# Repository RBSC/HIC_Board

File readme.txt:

--------------------------------------------------------------------------------
HIC Board version 1.2
Copyright (c) 2021-2023 RBSC
Last updated: 21.09.2023
--------------------------------------------------------------------------------

About
-----

It's a well-known fact that certain MSX2/2+ computers have a so-called "HIC Board" - the special "Hybrid IC" daughterboard that is
mounted onto the MSX computer's motherboard and provides certain functionality. This functionality is as follows:

 - converts RGBS signals to composite video
 - pre-amplifies and buffers audio
 - mutes audio at startup and on pause to prevent clicks
 - mixes all audio inputs
 - amplifies and buffers the cassette interface signals
 - buffers cassette interface's relay operations

This board is known to be installed in the following MSX computers:

 - Sony HB-F1II
 - Sony HB-F1XD
 - Sony HB-F1XV
 - Sony HB-F1XDJ
 - Sony HB-F1XDmkII
 - Panasonic FS-A1mkII
 - Panasonic FS-A1F
 - Kawai KMC-5000 (Panasonic FS-A1F OEM)

Normally, the board works just fine, but there's a problem with 3 electrolytic capacitors - they leak and damage the board,
sometimes beyond repair. Fixing the leaked boards is difficult as some components can separate from the corroded solder pads,
some tracks can be corroded under the CXA chip resulting in the board's malfunction.

The original HIC board's schematics and layout can be found here:
http://elec-junker-p2.blog.jp/MITSUMI%20EMC-NX0039_REV02_PU.pdf

HIC Board's Redesign
--------------------

Taking into account all the above listed problems, it was decided to clone the HIC board and at the same time add the following
improvements:

 - use a better and commonly available encoder chip CXA2075
 - add s-video output capability
 - try to get rid of the original 4069UBF chip's dependency
 - make the HIC board detachable

It was also desired to get rid of the 2 special components: IMN10 and FMW1, but they appeared to be still available for purchasing,
so they remained on the redesigned board.

During the redesign there appeared a few problems. The 4069UBF chip from Toshiba was used by the original engineers as an amplifier,
so the board's audio and cassette interface operations were dependent on certain features of that chip. When trying to replace this
chip with similar ones, for example 74LS04 or 74HCT04, the audio functionality was crippled. The only possible replacement appears
to be 74HC04 with 68pF capacitor added between pins 3 and 7 (GND). See the "74hc04_fix.jpg" image in the Pics folder.

The optional resistor R35 should not be installed unless the cassette input circuit doesn't work as desired.

Please note that R39 should be 0 Ohm resistor for all computers except for HB-F1XDJ. On that particular computer R39 should
be 220k.

Where to buy parts
------------------

At the time of this readme's creation the parts are available from the following sellers:

 - pin headers (male and female): https://www.aliexpress.com/item/4001122376295.html
 - CXA2075 encoder: https://www.aliexpress.com/item/33020885081.html
 - 4069UBF: https://www.aliexpress.com/item/1005002494421415.html
 - 68uH inductor: https://www.aliexpress.com/item/1005002963165525.html
 - LMV358M amplifier: https://www.aliexpress.com/item/4001116443945.html
 - 68pF trim capacitor: https://www.aliexpress.com/item/4000222152928.html
 - 2SA1037 transistor: https://www.aliexpress.com/item/1005002503421569.html
 - 2SC2411 transistor: https://www.aliexpress.com/item/1005004568437670.html
 - IMN10: https://www.aliexpress.com/item/1005004322498640.html
 - FMW1: https://www.ebay.com/itm/325038640119 or from Wierzbowsky (RBSC)

The resistors and capacitors 0805 and 1210 form factor can be ordered from any reasonable seller. The boards can be ordered from the
JLCPCB.COM factory.

IMPORTANT!
----------

The board hasn't been tested on all available MSX2/MSX2+ computers that are listed above. So far, the board was proved to be working
well on Panasonic A1 series computers, as well as on Sony F1-XV. There's still no feedback from some people who bought the HIC board
kits for other computers. As a result, the project's status is still WIP (work in progress).

The boards version 1.0 and 1.1 have an error that results in problems with PSG and FM sound on Sony HB-F1XDJ. The information on how
to fix the problem with those boards can be found in the "v1_board_fix.jpg" image file. One trace needs to be cut, 2 pads need to be
connected and C20 needs to be replaced with 39pF capacitor.

The RBSC provides all the files and information for free, without any liability (see the disclaimer.txt file). The provided information,
software or hardware must not be used for commercial purposes unless permitted by the RBSC. Producing a small amount of bare boards for
personal projects and selling the rest of the batch is allowed without the permission of RBSC.

When the sources of the tools are used to create alternative projects, please always mention the original source and the copyright!

Contact information
-------------------

The members of RBSC group Tnt23, Wierzbowsky, Pyhesty, Ptero, GreyWolf, SuperMax, VWarlock and DJS3000 can be contacted via the group's
e-mail address:

info@rbsc.su

The group's coordinator could be reached via this e-mail address:

admin@rbsc.su

The group's website can be found here:

https://rbsc.su/
https://rbsc.su/ru

The RBSC's hardware repository can be found here:

https://github.com/rbsc

The RBSC's 3D model repository can be found here:

https://www.thingiverse.com/groups/rbsc/things

-= ! MSX FOREVER ! =-

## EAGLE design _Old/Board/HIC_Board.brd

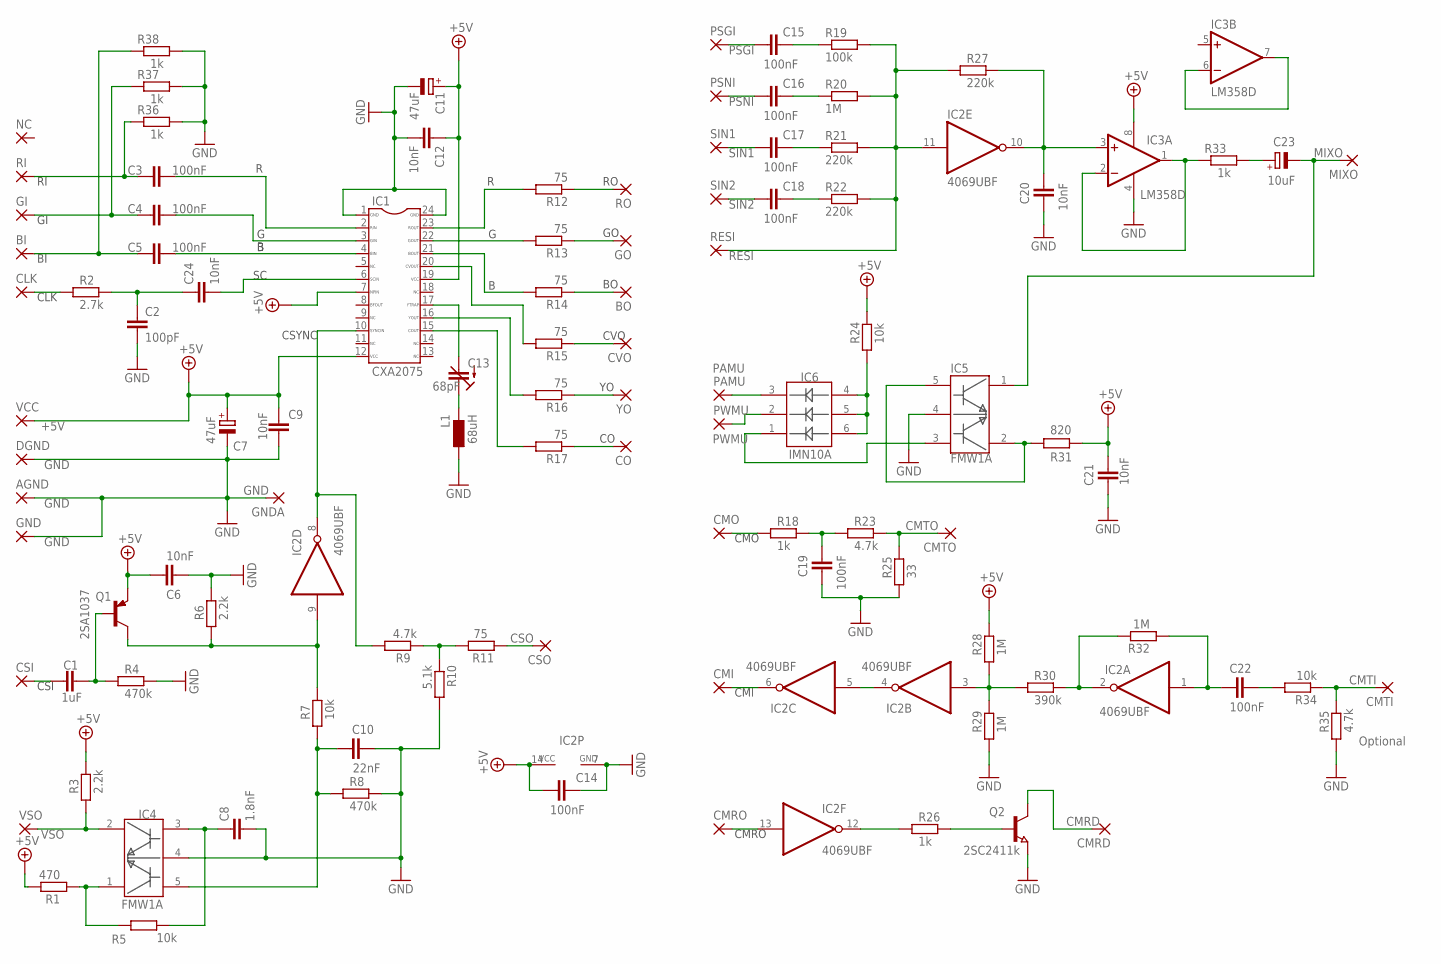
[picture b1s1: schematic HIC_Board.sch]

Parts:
AGND: HICPADSMD; SMD1,27-2,54
BI: HICPADSMD; SMD1,27-2,54
BO: HICPADSMD; SMD1,27-2,54
C1: 1uF; C1210
C2: 100pF; C0805
C3, C4, C5, C14, C15, C16, C17, C18, C19, C22: 100nF; C0805
C6, C9, C12, C20, C21, C24: 10nF; C0805
C7, C11: 47uF; SMC_B
C8: 1.8nF; C0805
C10: 22nF; C0805
C13: 68pF; CTRIMTZ03
C23: 10uF; SMC_B
CLK: HICPADSMD; SMD1,27-2,54
CMI: HICPADSMD; SMD1,27-2,54
CMO: HICPADSMD; SMD1,27-2,54
CMRD: HICPADSMD; SMD1,27-2,54
CMRO: HICPADSMD; SMD1,27-2,54
CMTI: HICPADSMD; SMD1,27-2,54
CMTO: HICPADSMD; SMD1,27-2,54
CO: HICPADSMD; SMD1,27-2,54
CSI: HICPADSMD; SMD1,27-2,54
CSO: HICPADSMD; SMD1,27-2,54
CVO: HICPADSMD; SMD1,27-2,54
DGND: HICPADSMD; SMD1,27-2,54
GI: HICPADSMD; SMD1,27-2,54
GND: HICPADSMD; SMD1,27-2,54
GNDA: HICPADSMD; SMD1,27-2,54
GO: HICPADSMD; SMD1,27-2,54
IC1: CXA2075; SOP24
IC2: 4069UBF; SO14
IC3: LM358D; SO08
IC4, IC5: FMW1A; SMT5
IC6: IMN10A; SMT6
L1: 68uH; L3225M
MIXO: HICPADSMD; SMD1,27-2,54
NC: HICPADSMD; SMD1,27-2,54
PAMU: HICPADSMD; SMD1,27-2,54
PSGI: HICPADSMD; SMD1,27-2,54
PSNI: HICPADSMD; SMD1,27-2,54
PWMU: HICPADSMD; SMD1,27-2,54
Q1: 2SA1037; SOT23
Q2: 2SC2411k; SOT23
R1: 470; R0805
R2: 2.7k; R0805
R3, R6: 2.2k; R0805
R4, R8: 470k; R0805
R5, R7, R24, R34: 10k; R0805
R9, R23, R35: 4.7k; R0805
R10: 5.1k; R0805
R11, R12, R13, R14, R15, R16, R17: 75; R0805
R18, R26, R33, R36, R37, R38: 1k; R0805
R19: 100k; R0805
R20, R28, R29, R32: 1M; R0805
R21, R22, R27: 220k; R0805
R25: 33; R0805
R30: 390k; R0805
R31: 820; R0805
RESI: HICPADSMD; SMD1,27-2,54
RI: HICPADSMD; SMD1,27-2,54
RO: HICPADSMD; SMD1,27-2,54
SIN1, SIN2: HICPADSMD; SMD1,27-2,54
VCC: HICPADSMD; SMD1,27-2,54
VSO: HICPADSMD; SMD1,27-2,54
YO: HICPADSMD; SMD1,27-2,54

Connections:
+5V: C6.1, C7.+, C9.2, C11.+, C12.1, C14.2, C21.2, IC1.7, IC1.12, IC1.19, IC2.14 (VCC), IC3.8 (V+), Q1.2 (E), R1.2, R3.2, R24.2, R28.2, R31.2, VCC.1
CMRD: CMRD.1, Q2.3 (C)
CMTI: CMTI.1, R34.1, R35.2
CMTO: CMTO.1, R23.2, R25.2
CSO: CSO.1, R11.1
GND: AGND.1, C2.1, C6.2, C7.-, C8.1, C9.1, C10.2, C11.-, C12.2, C14.1, C19.2, C20.2, C21.1, DGND.1, GND.1, GNDA.1, IC1.1, IC1.24, IC2.7 (GND), IC3.4 (V-), IC4.4, IC5.4, L1.1, Q2.2 (E), R4.2, R6.2, R8.2, R10.2, R25.1, R29.1, R35.1, R36.2, R37.2, R38.2
MIXO: C23.-, IC5.1, MIXO.1
unnamed: IC1.23, R12.2
unnamed: IC1.22, R13.2
unnamed: IC1.21, R14.2
unnamed: R12.1, RO.1
unnamed: GO.1, R13.1
unnamed: C3.1, R36.1, RI.1
unnamed: C4.1, GI.1, R37.1
unnamed: BO.1, R14.1
unnamed: R16.1, YO.1
unnamed: CVO.1, R15.1
unnamed: C2.2, C24.2, R2.2
unnamed: C1.2, CSI.1
unnamed: CLK.1, R2.1
unnamed: C13.1 (E), L1.2
unnamed: IC1.16, R16.2
unnamed: CMO.1, R18.1
unnamed: CMI.1, IC2.6 (O)
unnamed: C19.1, R18.2, R23.1
unnamed: IC2.4 (O), IC2.5 (I)
unnamed: C13.2 (A), IC1.17
unnamed: IC2.3 (I), R28.1, R29.2, R30.1
unnamed: CMRO.1, IC2.13 (I)
unnamed: IC2.2 (O), R30.2, R32.2
unnamed: C22.1, IC2.1 (I), R32.1
unnamed: C22.2, R34.2
unnamed: IC2.12 (O), R26.1
unnamed: Q2.1 (B), R26.2
unnamed: C17.2, R21.1
unnamed: C15.2, R19.1
unnamed: C16.2, R20.1
unnamed: C18.2, R22.1
unnamed: C20.1, IC2.10 (O), IC3.3 (+IN), R27.2
unnamed: C23.+, R33.2
unnamed: IC3.6 (-IN), IC3.7 (OUT)
unnamed: IC5.2, IC5.5, R31.1
unnamed: IC5.3, IC6.1
unnamed: IC6.4, IC6.5, IC6.6, R24.1
unnamed: C1.1, Q1.1 (B), R4.1
unnamed: IC3.1 (OUT), IC3.2 (-IN), R33.1
unnamed: IC2.9 (I), Q1.3 (C), R6.1, R7.2
unnamed: C8.2, IC4.3, R5.2
unnamed: BI.1, C5.1, R38.1
unnamed: C4.2, IC1.3
unnamed: C3.2, IC1.2
unnamed: C5.2, IC1.4
unnamed: IC1.10, IC2.8 (O), R9.2
unnamed: IC4.1, R1.1, R5.1
unnamed: R9.1, R10.1, R11.2
unnamed: C10.1, IC4.5, R7.1, R8.1
unnamed: C24.1, IC1.6
unnamed: IC1.20, R15.2
unnamed: CO.1, R17.1
unnamed: IC1.15, R17.2
PAMU: IC6.3, PAMU.1
PSGI: C15.1, PSGI.1
PSNI: C16.1, PSNI.1
PWMU: IC6.2, PWMU.1
RESI: IC2.11 (I), R19.2, R20.2, R21.2, R22.2, R27.1, RESI.1
SIN1: C17.1, SIN1.1
SIN2: C18.1, SIN2.1
VSO: IC4.2, R3.1, VSO.1

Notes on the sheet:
CSYNC
CVO
CLK
CMO
CMI
CMRO
CSI
Optional

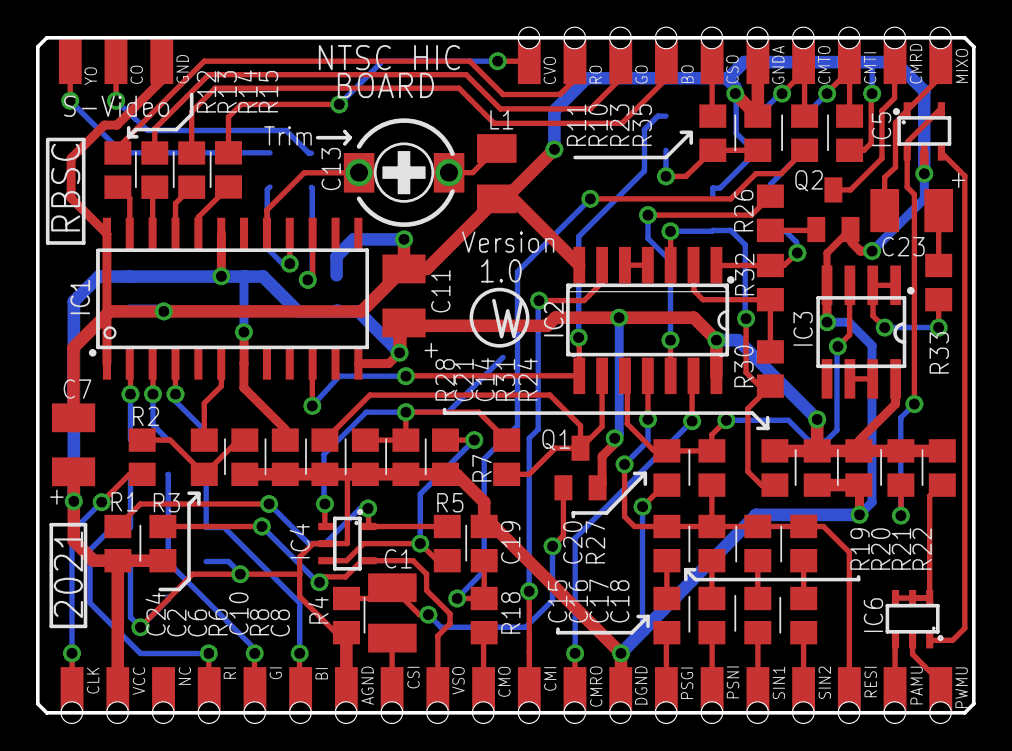
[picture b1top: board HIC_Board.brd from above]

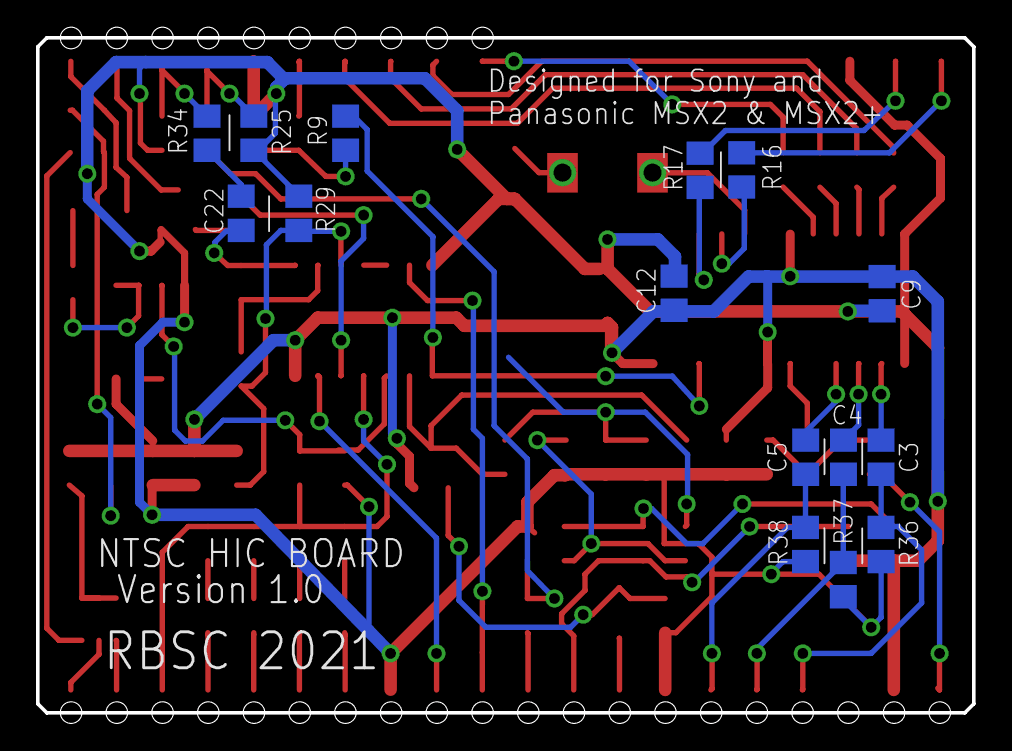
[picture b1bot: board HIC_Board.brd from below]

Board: 2 copper layers, 52.0 x 37.5 mm, 104 parts (15 on the bottom side), 68 nets.

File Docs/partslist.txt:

Partlist
--------

Part     Value          Device               Package      Library         Sheet

C1       1uF            C-EUC1210            C1210        rcl             1
C2       100pF          C-EUC0805            C0805        rcl             1
C3       100nF          C-EUC0805            C0805        rcl             1
C4       100nF          C-EUC0805            C0805        rcl             1
C5       100nF          C-EUC0805            C0805        rcl             1
C6       10nF           C-EUC0805            C0805        rcl             1
C7       47uF           CPOL-EUSMCB          SMC_B        rcl             1
C8       1.8nF          C-EUC0805            C0805        rcl             1
C9       10nF           C-EUC0805            C0805        rcl             1
C10      22nF           C-EUC0805            C0805        rcl             1
C11      47uF           CPOL-EUSMCB          SMC_B        rcl             1
C12      10nF           C-EUC0805            C0805        rcl             1
C13      68pF           C-TRIMMTZ03          CTRIMTZ03    rcl             1
C14      100nF          C-EUC0805            C0805        rcl             1
C15      100nF          C-EUC0805            C0805        rcl             1
C16      100nF          C-EUC0805            C0805        rcl             1
C17      100nF          C-EUC0805            C0805        rcl             1
C18      100nF          C-EUC0805            C0805        rcl             1
C19      100nF          C-EUC0805            C0805        rcl             1
C20      39pF           C-EUC0805            C0805        rcl             1
C21      10nF           C-EUC0805            C0805        rcl             1
C22      100nF          C-EUC0805            C0805        rcl             1
C23      10uF           CPOL-EUSMCB          SMC_B        rcl             1
C24      10nF           C-EUC0805            C0805        rcl             1
IC1      CXA2075        CXA2075              SOP24        CXA2075M        1
IC2      4069UBF        74HCT04D             SO14         74xx-eu         1
IC3      LM358D         LM358D               SO08         linear          1
IC4      FMW1A          FMW1A                SMT5         fmw1            1
IC5      FMW1A          FMW1A                SMT5         fmw1            1
IC6      IMN10A         IMN10A               SMT6         imn10           1
L1       68uH           LL3225M              L3225M       eagle-ltspice   1
Q1       2SA1037        BCX71SMD             SOT23        transistor-pnp  1
Q2       2SC2411k       NPN-TRANSISTOR_SOT23 SOT23        semicon-smd-ipc 1
R1       470            R-EU_R0805           R0805        rcl             1
R2       2.7k           R-EU_R0805           R0805        rcl             1
R3       2.2k           R-EU_R0805           R0805        rcl             1
R4       470k           R-EU_R0805           R0805        rcl             1
R5       10k            R-EU_R0805           R0805        rcl             1
R6       2.2k           R-EU_R0805           R0805        rcl             1
R7       10k            R-EU_R0805           R0805        rcl             1
R8       470k           R-EU_R0805           R0805        rcl             1
R9       4.7k           R-EU_R0805           R0805        rcl             1
R10      5.1k           R-EU_R0805           R0805        rcl             1
R11      75             R-EU_R0805           R0805        rcl             1
R12      75             R-EU_R0805           R0805        rcl             1
R13      75             R-EU_R0805           R0805        rcl             1
R14      75             R-EU_R0805           R0805        rcl             1
R15      75             R-EU_R0805           R0805        rcl             1
R16      75             R-EU_R0805           R0805        rcl             1
R17      75             R-EU_R0805           R0805        rcl             1
R18      1k             R-EU_R0805           R0805        rcl             1
R19      100k           R-EU_R0805           R0805        rcl             1
R20      1M             R-EU_R0805           R0805        rcl             1
R21      220k           R-EU_R0805           R0805        rcl             1
R22      220k           R-EU_R0805           R0805        rcl             1
R23      4.7k           R-EU_R0805           R0805        rcl             1
R24      10k            R-EU_R0805           R0805        rcl             1
R25      33             R-EU_R0805           R0805        rcl             1
R26      1k             R-EU_R0805           R0805        rcl             1
R27      220k           R-EU_R0805           R0805        rcl             1
R28      1M             R-EU_R0805           R0805        rcl             1
R29      1M             R-EU_R0805           R0805        rcl             1
R30      390k           R-EU_R0805           R0805        rcl             1
R31      820            R-EU_R0805           R0805        rcl             1
R32      1M             R-EU_R0805           R0805        rcl             1
R33      1k             R-EU_R0805           R0805        rcl             1
R34      10k            R-EU_R0805           R0805        rcl             1
R35      4.7k           R-EU_R0805           R0805        rcl             1
R36      1k             R-EU_R0805           R0805        rcl             1
R37      1k             R-EU_R0805           R0805        rcl             1
R38      1k             R-EU_R0805           R0805        rcl             1
R39      0 Ohm/220k     R-EU_R0805           R0805        rcl             1

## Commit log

2022-08-14 :confetti_ball: Added .gitattributes & .gitignore files
2022-08-14 Initial release 14.08.2022
    Initial release of the board v1.0
2022-08-14 Initial release 14.08.2022
    Initial release of the v1.0 board
2022-08-16 Updated 16.08.2022
    Updated readme.txt
2023-09-20 Updated 21.09.2023
    Updated to v1.2. The error was fixed, the resistor was added for HB-F1XDJ computer (see the readme file)
2023-09-20 Added old release files
    Old release files v1.0

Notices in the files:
Board/HIC_Board.sch:
Re-engineering and improvements by RBSC (c) 2021-2023
